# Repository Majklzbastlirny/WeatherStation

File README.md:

# WeatherStation
# NEEDS ESP32 ver. 2.0.0 (as Arduino board) otherwise light sensor will NOT work
Weather Station with ESP32, ESP8266, MQTT, InfluxDB and Grafana.

This is my maturita (finals) project.

Public API: https://weatherapi.majkl.tk

Public dashboard https://grafana.majkl.tk

Twitter (new data uploaded every second hour): https://twitter.com/majklzbastlirny

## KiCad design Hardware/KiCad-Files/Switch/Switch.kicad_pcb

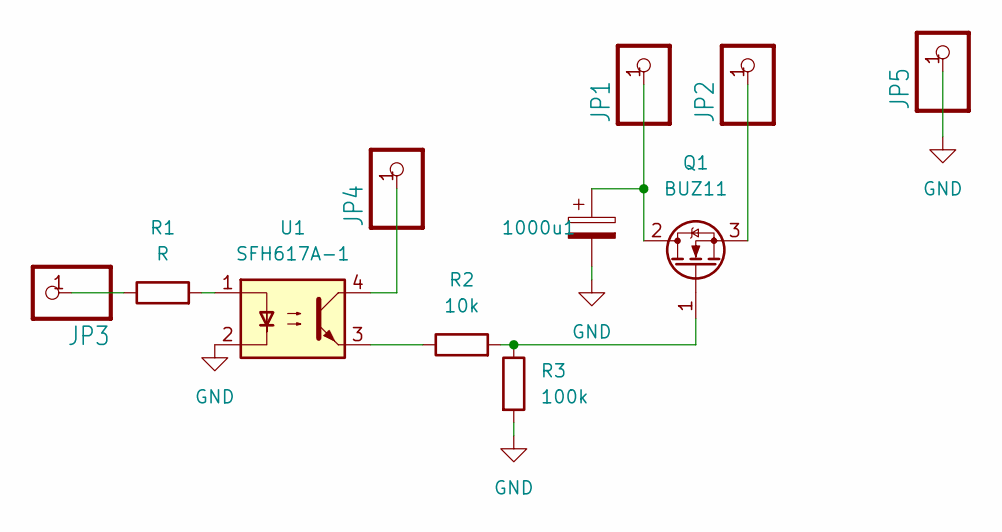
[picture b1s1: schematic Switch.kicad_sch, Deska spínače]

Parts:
1000u1: C_Polarized; CP_Radial_D10.0mm_P5.00mm
JP1, JP2, JP3, JP4, JP5: PINHD-1X1; Pin_D0.7mm_L6.5mm_W1.8mm_FlatFork
Q1: BUZ11; TO-220-3_Vertical
R1: R; R_Axial_DIN0207_L6.3mm_D2.5mm_P10.16mm_Horizontal
R2: 10k; R_Axial_DIN0207_L6.3mm_D2.5mm_P10.16mm_Horizontal
R3: 100k; R_Axial_DIN0207_L6.3mm_D2.5mm_P10.16mm_Horizontal
U1: SFH617A-1; DIP-4_W7.62mm

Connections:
GND: 1000u1.2, JP5.1, R3.2, U1.2
unnamed: 1000u1.1, JP1.1, Q1.2 (D)
unnamed: JP2.1, Q1.3 (S)
unnamed: JP3.1, R1.1
unnamed: JP4.1, U1.4
unnamed: Q1.1 (G), R2.2, R3.1
unnamed: R1.2, U1.1
unnamed: R2.1, U1.3

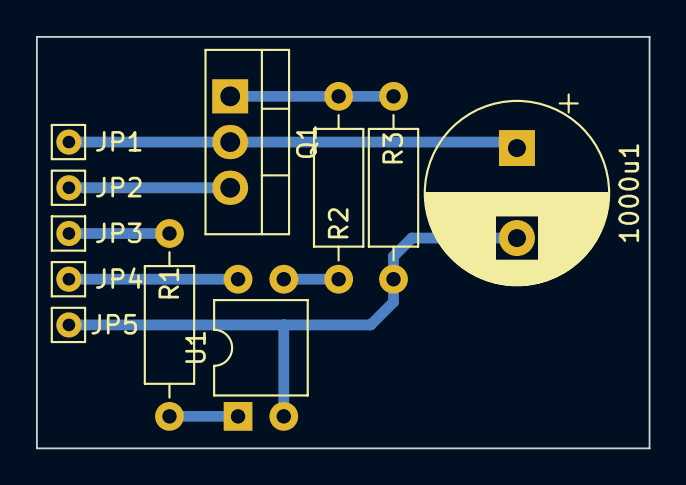
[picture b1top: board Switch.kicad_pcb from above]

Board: 2 copper layers, 34.0 x 22.9 mm, 11 parts (0 on the bottom side), 8 nets.

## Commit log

2021-06-17 Lightweight version - only temp & humidity.
2021-06-17 WORK ONLY ON ESP8266.
    Currently trying to port code to ESP32
2021-06-17 Flow for Node-RED
2021-08-28 "Smol update"
    Added drawing, how it may look like. 3D files will be included, when they will be perfect for me
2021-08-30 Created MAIN file
    This file will be used in main Weather Station
2021-08-30 Large update
    defined most of things
2021-09-10 HELLHOLE
    https://youtu.be/J3VIh5Vz2WE?t=5
2021-09-23 Rain detector pcb
2021-09-30 Added ESP-32 module for use in Sprint-Layout
2021-10-01 NOW WORKING
    Had to change pin numbers to accomodate serial communication. after testing on breadboard IT WORKS!
2021-10-01 Create ESP-32_Sprint-Layout_Macro.lay6.bak
    Backup file created automatically by Sprint Layout
2021-10-01 Added bunch of samples
2021-10-02 DHT22 sample works
2021-10-02 BH1750 sample works
2021-10-02 works on arduino uno/nano. not ESP32
2021-10-03 Anemometer reading works.
    debounce NEEDED
2021-10-05 Reduced code
    Purged useless functions
2021-10-05 ML8511 for ESP32
    needed due to 3v3 logic levels
2021-10-07 WORKING code for ML8511
    after 2 hours -_-
2021-10-07 NOT WORKING
2021-10-21 New combined - WORKING
2021-10-24 Now fast as hell + reset
2021-11-02 Added UV reading capabilities
2021-11-02 Header update.
2021-11-02 Added images
2021-11-04 Added wind vane code
2021-11-09 I like to move it move it
2021-11-09 backup of Main_board
2021-11-09 Start of the PCB
2021-11-16 Making it neater pt.1
2021-11-18 Large update
2021-11-18 Made terminal output lookin nice
2021-11-18 Prepairing for deep sleep
2021-11-19 Added Deep sleep
2021-11-20 Added toggling for serial output
2021-11-20 Added support for wind speed (not yet working)
2021-11-20 quick fix
2021-11-20 modified variables and reached 500 lines of code
2021-11-20 Anemometer WORKS
2021-11-23 Probably final update, since it sould be working
2021-11-23 Added Heating and Sensor turnoff
2021-11-24 IT FULLY WORKS
2021-11-25 Updated Backup files
2021-11-25 Created Light sensor board
2021-11-25 Added bunch of Sprint Layout macros
2021-11-25 Created board
2021-11-26 Placed components
2021-11-27 Looks nasty, but it works
2021-11-27 Rename Combined.ino to WeatherStation_Main.ino
2021-11-27 Rename Combined/WeatherStation_Main.ino to WeatherStation_Main/WeatherStation_Main.ino
2021-11-27 Works!
2021-11-29 Rename flows.json to NodeRED/flows.json
2021-11-29 Cleaning up
2021-11-29 Cleaning up a bit
2021-11-29 Moved ESP, Anemo not yet connected, implement charger
2021-11-29 3v3 stab NEEDED
2021-11-30 General update
2021-12-02 added ports for btree and solar
2021-12-05 Lead battery charger with 723
2021-12-05 updaate
2021-12-06 Slowly adding stuff
2021-12-07 Update
    Added charger
2021-12-07 Nearly finished
2021-12-17 Bouta finnish
2021-12-24 update for BME280
2021-12-29 Trying making files in kicad for easier viewing
2021-12-29 Getting ready for final update
    UV needs fixing and heating too
2021-12-29 Updated deprecated
2021-12-29 Rename WeatherStation_Home-Unit/WeatherStation_Home-Unit.ino to WeatherStation_Home-Unit_Main/WeatherStation_Home-Unit_Main.ino
2021-12-29 Moving
2021-12-29 create directory
2021-12-29 Rename WeatherStation_Home-Unit_Main.ino to WeatherStation_Home-Unit_Slave.ino
2022-01-11 Prepairing for heating
2022-01-12 Heating works
    Only cleanup remains
2022-01-17 Working.
    Heating system yet not coded properly in.
2022-01-17 Photos
2022-01-17 Create THIS IS NO LONGER UPDATED
2022-01-22 sample
2022-01-22 Update back to BMP280
2022-01-22 Not working fix for BMP280
2022-01-24 Smol update
2022-01-26 Created python script
    It's for pulling latest data and showing them. later this will be displaying results as JSON
2022-01-26 Successfully outputting JSON
2022-01-27 Removed unused dependencies
2022-01-27 Move
2022-01-28 Fully working
2022-01-29 Added Dew point and wind chill
    But not really working
2022-01-29 Repaired heatindex
2022-01-29 Added ignore for worthless metrics
2022-01-29 Clearing up and sorting stuff
2022-01-30 Rename Used_Libraries.txt to Arduino_Used_Libraries.txt
2022-01-31 Rename Code/WeatherStation_Home-Unit_Slave/WeatherStation_Home-Unit_Slave.ino to Code/WeatherStation_Home-Unit_Influx/WeatherStation_Home-Unit_Influx.ino
2022-01-31 Fixed bug with negative values
2022-01-31 Somewhat works
2022-02-04 a lot
2022-02-05 probably not working
2022-02-05 Looks promising
2022-02-05 Made it more readable over MQTT
2022-02-06 Made it compatible with FTDI programmers. + deep sleep reset
2022-02-07 Working on 1st page
2022-02-15 Large update. Made it more effitient and readable
2022-02-16 Probably final update
2022-02-16 WORKS
2022-02-16 Added restart when no WIFI
2022-02-18 Fixed domain
2022-02-22 Nearly "production" ready
2022-02-22 Simple PHP parser
2022-02-22 Rename
2022-02-26 Trying KiCad
2022-02-27 Added additional resources
2022-02-27 Somehow it works
2022-02-27 Addded sleep when no WIFI
2022-02-28 Added fonts
2022-02-28 Now shows accurate time even offline (with prior sync)
2022-03-01 Arrded Fonts
2022-03-01 Removed Fonts
2022-03-01 Added Font
2022-03-01 Added photo of MAX
    (My dog)
2022-03-01 Added "awake" photo of my dog
2022-03-01 Added second dog picture (changing based on time)
2022-03-02 Added back seconds
2022-03-02 Creating/modifying PCB and Schematic
2022-03-04 Fixed typo
2022-03-04 Added photos to documentation
2022-03-04 removed blurry photos
2022-03-06 Added longer sleep and fixed long date overflow
2022-03-06 Solving bug with DHT22
2022-03-08 Making it neater to look at
2022-03-08 Added new pictures
2022-03-08 Added (hopefully) last pictures
2022-03-13 Made it neater
2022-03-13 Added custom text when no wind
2022-03-13 added pictures
2022-03-14 new and updated
2022-03-20 Another update
2022-03-24 Repaired code
2022-03-24 Added heating on start
2022-03-29 Final UPDATE
2022-03-30 Added 3d printable files
2022-04-04 Presentation
2022-04-16 one of last updates for school part
2022-04-21 Updated presentation
2022-04-21 new stuph
2022-05-12 Update 4 days before finals
2022-06-12 bugfixes
2022-08-29 Added heat index to EInk display
